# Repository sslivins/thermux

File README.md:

# Thermux

A multi-sensor temperature monitoring system for ESP32-POE boards with Home Assistant integration via MQTT auto-discovery. **Supports 20 DS18B20 sensors on a single 1-Wire bus by default, configurable up to 100** (`CONFIG_MAX_SENSORS`) - perfect for monitoring multiple zones, equipment, or environments from one device.

## Features

- **Up to 100 DS18B20 Sensors** - Monitor multiple temperature points from a single device on one 1-Wire bus (20 by default; raise `CONFIG_MAX_SENSORS` in menuconfig, max 100)
- **Optimized Parallel Reads** - Uses 1-Wire skip ROM command to read all sensors simultaneously (~1050ms for 20 sensors in 12-bit mode, ~450ms in 9-bit)
- **Home Assistant Integration** - MQTT auto-discovery for seamless integration
- **Modbus TCP** - Optional read-only Modbus TCP server so PLCs and heat pump controllers can read temperatures directly (see [Modbus TCP](#modbus-tcp))
- **BACnet/IP** - Optional read-only BACnet/IP server for building-automation systems (see [BACnet/IP](#bacnetip))
- **Web Interface** - Configuration and monitoring via built-in web server
- **Sensor Identification** - Change detection highlighting helps identify which physical sensor is which
- **Custom Sensor Names** - Assign friendly names to sensors via web UI (persisted in NVS)
- **OTA Updates** - Over-the-air firmware updates from GitHub releases or manual upload with progress display, including a native Home Assistant firmware **update entity** with an Install button and progress bar
- **Ethernet & WiFi** - Primary Ethernet with WiFi fallback
- **mDNS** - Access via `thermux.local` (auto-increments on collision: thermux-2.local, etc.)
- **Service Discovery** - Discoverable via `_thermux._tcp` and `_http._tcp` services
- **Web-based Logs** - View system logs without serial connection (16KB circular buffer)
- **Bus Error Tracking** - Monitor 1-Wire CRC error rates per sensor and globally via web UI and Home Assistant
- **Runtime Log Level Control** - Change log verbosity via web UI without reflashing
- **Session-based Authentication** - Optional password protection with login page
- **API Key Authentication** - Stateless API access for scripts and automation

## Hardware Requirements

- **Board**: [Olimex ESP32-POE-ISO](https://www.olimex.com/Products/IoT/ESP32/ESP32-POE-ISO/) (or compatible ESP32-POE board)
- **Sensors**: DS18B20 1-Wire temperature sensors
- **Connection**: Sensors connected to GPIO4 (configurable in menuconfig)
- **PCB** (optional): Custom breakout board - see [hardware/](hardware/) for KiCad files and BOM
- **Enclosure** (optional): 3D printable case - see [enclosure/](enclosure/) for print files

### Wiring

| DS18B20 Pin | ESP32-POE |
|-------------|-----------|
| VCC (Red)   | 3.3V      |
| GND (Black) | GND       |
| DATA (Yellow) | GPIO4   |

> **Note**: A 4.7kΩ pull-up resistor is required between DATA and VCC. For 10+ sensors, use 2.2kΩ or 1.5kΩ to ensure reliable bus communication (the ESP32's internal pull-up is too weak for 1-Wire).

## Installation

### Pre-built Firmware (Recommended)

Download the latest firmware from [GitHub Releases](https://github.com/sslivins/thermux/releases/latest) and follow the [FLASHING.md](FLASHING.md) guide.

**For brand new ESP32-POE devices**, you'll need all three files:
- `bootloader.bin`
- `partition-table.bin`
- `thermux.bin`

**For OTA updates** on devices already running Thermux, use the web interface at `http://thermux.local/ota` - it downloads and installs updates automatically (no manual file download needed). You can also manually upload a specific `thermux.bin` version if desired.

See [FLASHING.md](FLASHING.md) for detailed instructions.

### Building from Source

#### Prerequisites

- [ESP-IDF v5.5.x](https://docs.espressif.com/projects/esp-idf/en/latest/esp32/get-started/)
- VS Code with ESP-IDF extension (recommended)

#### Build & Flash

```bash
# Set target
idf.py set-target esp32

# Build
idf.py build

# Flash
idf.py -p COMx flash monitor
```

Or use the ESP-IDF VS Code extension build/flash commands.

## Configuration

After flashing, access the web interface at `http://thermux.local` or the device IP.

> **Note**: If multiple devices are on the network, subsequent devices will be `thermux-2.local`, `thermux-3.local`, etc.

### Web Interface Pages

- **/** - Dashboard with live temperature readings
- **/config** - Configuration settings (MQTT, WiFi, sensor intervals, OTA)
- **/ota** - Manual firmware upload

### Configuration Options

| Setting | Description |
|---------|-------------|
| **MQTT Broker** | Home Assistant MQTT broker address |
| **MQTT Port** | Broker port (default: 1883) |
| **MQTT Username/Password** | Authentication credentials |
| **WiFi SSID/Password** | Fallback WiFi credentials |
| **Read Interval** | Sensor polling interval (seconds) |
| **Publish Interval** | MQTT publish interval (seconds) |
| **OTA URL** | GitHub releases URL for automatic updates |
| **Security** | Enable/disable password protection |

## REST API

Full API documentation is available as an OpenAPI 3.1 spec: [`docs/openapi.yaml`](docs/openapi.yaml)

View it interactively: [Swagger Editor](https://editor.swagger.io/?url=https://raw.githubusercontent.com/sslivins/thermux/main/docs/openapi.yaml)

## Home Assistant Integration

The device automatically registers sensors with Home Assistant via MQTT discovery. Each sensor appears as a temperature entity. Diagnostics include network status, uptime, seconds since the last successful bus read, consecutive failed bus cycles, and a rolling error rate across the most recent 1,000 reads. Lifetime read counters remain available as disabled-by-default engineering diagnostics.

### Firmware Update Entity

Thermux publishes a native Home Assistant **`update` entity** (device class `firmware`) via MQTT discovery. It shows the installed version, the latest available GitHub release, a link to the release notes, and an **Install** button that triggers the OTA download **with a live progress bar** — the same experience as updating any other HA device, no automation or REST command needed.

The entity is backed by these MQTT topics (base topic configurable, default `thermux`):

| Topic | Direction | Purpose |
|-------|-----------|---------|
| `homeassistant/update/thermux_firmware/config` | retained | Discovery config |
| `thermux/update/state` | device → HA (retained) | JSON: `installed_version`, `latest_version`, `release_url`, `update_percentage`, `in_progress` |
| `thermux/update/install` | HA → device | Payload `install` starts the OTA |

The device checks GitHub for new releases periodically (see `OTA_CHECK_INTERVAL_HOURS`) and updates the entity whenever availability or download progress changes.

### Manual REST Integration (Optional)

You can also poll sensors directly:

```yaml
# configuration.yaml
rest:
  - resource: http://thermux.local/api/sensors
    scan_interval: 60
    sensor:
      - name: "Temperature Sensor 1"
        value_template: "{{ value_json[0].temperature }}"
        unit_of_measurement: "°C"
        device_class: temperature
```

## Modbus TCP

Thermux can run a small, **read-only** Modbus TCP server so a PLC or heat pump controller can read temperatures without HTTP or JSON. It's off by default: turn it on under **Settings → Modbus TCP**, where you can also set the port (default 502) and unit ID (default 1).

Modbus has no password. Anyone on the network can read the registers, but nothing can be changed over Modbus, so only enable it on a network you trust.

### Sensor channels

Each sensor gets a **channel** (0–99) the first time it's seen, keyed by its ROM ID. A sensor keeps its channel when other sensors are added or removed, so a register address (and BACnet object) always refers to the same physical sensor. New sensors fill the lowest free channels, in ROM ID order. Modbus TCP and BACnet/IP share the same channels: channel N is input register 100+N and BACnet Analog Input N.

The **Settings → Sensor Channels** section shows each channel's Modbus register, BACnet object, sensor, and the status and temperature clients are currently reading. From there you can:

- **Move** a sensor to another channel. If that channel is in use, the two sensors swap.
- **Release** the channel of a sensor that has been disconnected, so the channel can be reused. Channels of connected sensors can't be released; they would just be reassigned on the next read.

Channels and Modbus settings are included in backups (**Settings → Backup**), so a replacement Thermux can serve the same register map.

### Register map

All registers are **input registers**, read with function code 04. Addresses are zero-based. All 100 channels are always mapped, whatever `CONFIG_MAX_SENSORS` is set to, so the map never changes between builds.

| Address | Contents |
|---------|----------|
| 0 | Map version (currently 1) |
| 1–3 | Firmware version: major, minor, patch |
| 4 | Channel capacity (always 100) |
| 5 | Read-cycle counter. Goes up by one after every scheduled read attempt, including failed ones; wraps at 65535 |
| 6–7 | Uptime in seconds (32-bit, register 6 is the high word) |
| 8–10 | Ethernet MAC address, two bytes per register (register 8 = byte 0 << 8 \| byte 1) |
| 11 | Firmware sensor limit (`CONFIG_MAX_SENSORS`) |
| 12 | Number of channels in use |
| 13 | Number of sensors found on the bus |
| 14 | Result of the last read cycle: 0 OK, 1 some sensors failed, 2 bus failure, 3 no sensors |
| 15 | Read interval in seconds |
| 100 + channel | Temperature in hundredths of a °C, signed 16-bit (2150 = 21.50 °C, 0xFF38 = −2.00 °C). **0x8000 whenever the status isn't OK** |
| 200 + channel | Status (see below) |
| 300 + channel | Seconds since the last successful read (capped at 65534). 65535 if the sensor has never been read or isn't connected |
| 1000 + 4 × channel | ROM ID, 4 registers per channel, two bytes per register in the same order as the address shown in the UI and API |

Channel status, checked in this order:

| Value | Meaning |
|-------|---------|
| 1 | Unassigned: no sensor in this channel |
| 2 | Missing: the sensor wasn't found in the latest bus scan |
| 3 | Read error: the sensor's latest read failed, or the whole read cycle failed |
| 4 | Stale: never read successfully, or the last good reading is older than 3 × the read interval (at least 30 s) |
| 0 | OK |

Use the age registers if you need a stricter freshness limit than the stale rule.

Each block (0–15, 100–199, 200–299, 300–399, 1000–1399) is separate. A read that covers an address outside those blocks, or runs from one block into the next, returns exception 0x02 (illegal data address). A single read can cover at most 125 registers, so the ROM block takes four reads.

### Reading a consistent set

A reading cycle can finish between two of your requests. To be sure the values you read all come from the same cycle, read register 5, read the blocks you need, then read register 5 again. If it changed, read again.

### Unit ID and errors

- Address requests to the configured unit ID (default 1). Unit ID 0 is also answered.
- Requests for any other unit ID get exception 0x0B (gateway target device failed to respond).
- Unit ID 255 isn't answered: the Modbus library Thermux uses (esp-modbus 2.1.3) drops it before it reaches the server. A fix has been submitted upstream ([espressif/esp-modbus#190](https://github.com/espressif/esp-modbus/pull/190)).
- Every function code other than 04, including all writes, gets exception 0x01 (illegal function).
- Up to 3 clients can be connected at once.

### Discovery

While the server is running, Thermux advertises it over mDNS as `_mbap._tcp`, with TXT records `unit` (unit ID), `id` (MAC address) and `map` (map version). Most PLCs don't use mDNS, so you'll usually enter the IP address and port by hand; give Thermux a DHCP reservation so the address doesn't change.

### Examples

The repo includes a small reader, `scripts/thermux_modbus.py` (needs `pip install pymodbus`). With just an address it decodes the whole map; `channel` reads specific channels; `raw` reads any range from any Modbus TCP device:

```bash
python scripts/thermux_modbus.py thermux.local               # device info + every channel
python scripts/thermux_modbus.py thermux.local --watch 5     # repeat every 5 s
python scripts/thermux_modbus.py thermux.local channel 3     # one channel: temperature, status, age, ROM ID
python scripts/thermux_modbus.py thermux.local channel 3 7   # several channels
python scripts/thermux_modbus.py thermux.local channel 3 --value   # just the °C value, for scripts
python scripts/thermux_modbus.py 192.168.1.50 --port 502 --unit 1 raw 100 6          # input registers
python scripts/thermux_modbus.py 192.168.1.50 raw 0 10 --fc 3                        # holding registers
```

[mbpoll](https://github.com/epsilonrt/mbpoll), temperatures of channels 0–5 (`-0` makes addresses zero-based):

```bash
mbpoll -m tcp -a 1 -0 -t 3 -r 100 -c 6 -1 thermux.local
```

Python with [pymodbus](https://github.com/pymodbus-dev/pymodbus) 3.9 or later (older versions use `slave=` instead of `device_id=`):

```python
from pymodbus.client import ModbusTcpClient

client = ModbusTcpClient("thermux.local", port=502)
client.connect()

def read(address, count):
    result = client.read_input_registers(address, count=count, device_id=1)
    if result.isError():
        raise RuntimeError(result)
    return result.registers

while True:
    cycle = read(5, 1)[0]
    temps = read(100, 10)
    status = read(200, 10)
    if read(5, 1)[0] == cycle:
        break

for channel, (raw, st) in enumerate(zip(temps, status)):
    if st == 0:
        celsius = (raw - 65536 if raw >= 32768 else raw) / 100
        print(f"channel {channel}: {celsius:.2f} °C")
```

## BACnet/IP

Thermux can also run a **read-only** BACnet/IP server, for building-automation systems that speak BACnet rather than Modbus. It's off by default: turn it on under **Settings → BACnet/IP**. Modbus and BACnet can run at the same time and serve the same sensor channels.

| Setting | Default | Notes |
|---------|---------|-------|
| UDP port | 47808 (0xBAC0) | The standard BACnet/IP port. Can't be the web server's port |
| Device instance | Derived from the Ethernet MAC | 0–4194302. Must be unique on the BACnet network, so set it by hand if your site has a numbering plan |
| Device name | The hostname | Up to 63 characters |

Like Modbus, BACnet has no password. Anyone on the network can read the objects, but nothing can be changed, so only enable it on a building-controls network you trust.

### Objects

The **Device** object reports vendor and model `Thermux`, the firmware version, and an object list.

Each assigned [sensor channel](#sensor-channels) is an **Analog Input**, and the instance number is the channel number. AI 3 is always channel 3, which is Modbus register 103. Unassigned channels have no object, so the object list only shows channels with a sensor.

| Property | Value |
|----------|-------|
| Object name | The sensor's friendly name, or `Channel N` if it has none. If two sensors have the same name, the second gets ` (N)` added, because BACnet object names must be unique |
| Description | The sensor's ROM ID, for example `281491BA00000069` |
| Present value | Temperature in °C. If a reading fails, the last good value stays and Reliability shows the fault |
| Units | degrees-Celsius |
| Reliability | `no-fault-detected` when OK; `no-sensor` when the sensor is missing; `communication-failure` on a read error; `unreliable-other` when the reading is stale |
| Status flags | `fault` is set whenever Reliability isn't `no-fault-detected` |
| COV increment | 0.1 °C |

When sensors are added, removed or renamed, the object list changes and the device's Database Revision goes up, so clients that cache the object list know to read it again.

### Services

- Who-Is / I-Am and Who-Has / I-Have
- ReadProperty and ReadPropertyMultiple
- SubscribeCOV (confirmed and unconfirmed), up to 16 subscriptions at once. Thermux sends a notification whenever a temperature changes by 0.1 °C or more, or its status flags change.

All write and management services (WriteProperty, CreateObject, ReinitializeDevice, DeviceCommunicationControl and so on) are rejected with `unrecognized-service`.

If the device's IP address changes (a new DHCP lease, for example), Thermux notices within a few seconds and sends a new I-Am. You don't need to restart anything.

### Example

The repo includes `scripts/thermux_bacnet.py`, which needs [BAC0](https://github.com/ChristianTremblay/BAC0) 2025 or later (`pip install BAC0`):

```bash
python scripts/thermux_bacnet.py --discover                       # Who-Is on the local network
python scripts/thermux_bacnet.py 192.168.1.50                     # device info and every Analog Input
python scripts/thermux_bacnet.py 192.168.1.50 --cov 60            # watch COV notifications for a minute
python scripts/thermux_bacnet.py 192.168.1.50 --try-write         # check that writes are rejected
python scripts/thermux_bacnet.py 192.168.1.50 --port 47809        # non-standard port
```

Add `--local 192.168.1.32/24` (your PC's address) if the script picks the wrong network interface. Who-Is discovery only finds devices on port 47808. On another port, I-Am replies are broadcast to that port, so give the address and `--port` instead.

## OTA Updates

Thermux can update three ways: the native Home Assistant **update entity** (above), the built-in **web interface**, or a **manual `.bin` upload**.

### Automatic Updates (Recommended)

The web interface can automatically download and install updates from GitHub releases:

1. Configure the OTA URL in web settings: `https://api.github.com/repos/sslivins/thermux/releases/latest`
2. Go to the OTA page and click "Check for Updates"
3. If a newer version is available, click "Update Now"
4. The device downloads, flashes, and reboots automatically - **no manual file download needed**

### Manual Upload

To install a **specific version** or **older version**, use the manual upload feature:

1. Download the desired `thermux.bin` from any [release](https://github.com/sslivins/thermux/releases)
2. Navigate to `/ota` page
3. Select the `.bin` firmware file
4. Click "Upload & Flash"

## Security

By default, the web interface is open (no authentication required). To enable password protection:

1. Go to `/config` → Security section
2. Check "Enable password protection"
3. Set username and password
4. Click "Save Security Settings"

When enabled, unauthorized access redirects to a login page. Sessions are stored in a cookie and expire after 7 days.

### API Key Authentication

For scripts and automation, use the API key instead of session cookies:

```bash
# Get sensor readings
curl -H "X-API-Key: YOUR_API_KEY" http://thermux.local/api/sensors

# Get device status
curl -H "X-API-Key: YOUR_API_KEY" http://thermux.local/api/status
```

The API key is:
- **Auto-generated** when authentication is first enabled
- **Visible** in Settings → Security section (click 📋 to copy)
- **Regeneratable** if compromised (click 🔄 to generate new key)
- **Persisted** across reboots in NVS flash

### Session Authentication

For browser-based access, the web UI uses session cookies. Protected API endpoints return `401 Unauthorized` with JSON body containing `{"login_required": true}` when not authenticated.

#### Auth Endpoints

| Endpoint | Method | Description |
|----------|--------|-------------|
| `/login` | GET | Login page (no auth required) |
| `/api/auth/login` | POST | Authenticate with `{"username":"...", "password":"..."}` |
| `/api/auth/logout` | POST | Destroy session |
| `/api/auth/status` | GET | Check if logged in |
| `/api/config/auth` | GET | Get auth config (includes API key) |
| `/api/config/auth/regenerate-key` | POST | Generate new API key |

### Home Assistant Integration

With API key authentication, REST integrations are straightforward:

```yaml
# configuration.yaml
rest:
  - resource: http://thermux.local/api/sensors
    headers:
      X-API-Key: "your-api-key-here"
    sensor:
      - name: "Pool Temperature"
        value_template: "{{ value_json.sensors[0].temperature }}"
        unit_of_measurement: "°C"
```

Alternatively, use the built-in MQTT integration with Home Assistant auto-discovery (no API key needed for MQTT).

## Technical Notes

### Optimized Temperature Reading

The firmware uses the 1-Wire **skip ROM** command (`0xCC`) to trigger temperature conversion on all DS18B20 sensors simultaneously, then reads each sensor individually. This reduces read time from O(n × delay) to O(delay + n × read):

| Sensors | Sequential (12-bit) | Parallel (12-bit) | Parallel (9-bit) |
|---------|---------------------|-------------------|-------------------|
| 1       | ~800ms              | ~800ms            | ~100ms            |
| 5       | ~4000ms             | ~850ms            | ~150ms            |
| 10      | ~8000ms             | ~900ms            | ~250ms            |
| 20      | ~16000ms            | ~1050ms           | ~450ms            |

The conversion delay depends on resolution: 12-bit = 750ms, 11-bit = 375ms, 10-bit = 188ms, 9-bit = 94ms. The parallel read overhead per sensor is minimal (~25ms for bus communication).

### Log Buffer

A 16KB circular buffer captures ESP-IDF logs for web display. Noisy system components (HTTP server internals, Ethernet MAC, etc.) are filtered to keep logs useful. The buffer can be viewed, cleared, and downloaded from the config page.

## Hardware Design

This repository includes open-source hardware designs:

### PCB ([hardware/](hardware/))

Two open-source KiCad boards:

- **Sensor Bus Hat** - plugs onto the ESP32-POE-ISO and breaks the 1-Wire bus out to RJ45 (carries the bus pull-up resistor)
- **Temperature Node** - DS18B20 breakout with RJ45 connectors for daisy-chaining sensors

- **KiCad project files** - Full schematic and PCB layout
- **Gerber files** - Ready for fabrication (JLCPCB, PCBWay, etc.)
- **Bill of Materials** - DigiKey part links

### Enclosure ([enclosure/](enclosure/))

3D printable cases, in two parts:

- **ESP32-POE-ISO Case** - the main enclosure; houses the ESP32-POE-ISO with the Sensor Bus Hat plugged on
- **Temperature Node** - two-part case (PCB + enclosure) for a distributed DS18B20 sensor node on the 1-Wire bus

Each is provided as:

- **Fusion 360** (.f3d / .f3z) - Parametric source files
- **STEP** (.step) - Universal CAD interchange format
- **Print files** (.3mf, .stl) - Ready for slicing

## Version History

See [GitHub Releases](https://github.com/sslivins/thermux/releases) for changelog.

## License

MIT License - See [LICENSE](LICENSE) for details.

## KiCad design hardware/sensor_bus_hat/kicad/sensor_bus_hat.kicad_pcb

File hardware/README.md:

# Hardware

Open-source PCB design files for Thermux. There are **two** boards:

- **Sensor Bus Hat** ([`sensor_bus_hat/`](sensor_bus_hat/)) — plugs onto the
  Olimex ESP32-POE-ISO and breaks the 1-Wire bus out to an RJ45 jack, carrying
  the bus pull-up resistor.
- **Temperature Node** ([`temp_node/`](temp_node/)) — the distributed DS18B20
  sensor breakout with RJ45 connectors for daisy-chaining sensors along the bus.

## Directory Structure

```
hardware/
├── sensor_bus_hat/     # ESP32-POE-ISO bus-adapter hat
│   ├── kicad/          # KiCad project (.kicad_pro, .kicad_sch, .kicad_pcb)
│   └── gerbers/        # Manufacturing files (gerbers, drills, BOM, CPL)
├── temp_node/          # DS18B20 sensor breakout node
│   ├── kicad/
│   └── gerbers/
└── README.md
```

Each board's `gerbers/` folder is self-contained — zip its contents (or upload
the folder) to JLCPCB / PCBWay to fabricate that board.

## Sensor Bus Hat

Adapter board that sits on the Olimex ESP32-POE-ISO and exposes the 1-Wire bus
on an RJ45 jack. It carries the bus **pull-up resistor** (see the pull-up note
below).

### Bill of Materials

| Qty | Designator | Description | Part Number |
|-----|-----------|-------------|-------------|
| 1 | R1 | Pull-up resistor, 4.7 kΩ (0805) — see pull-up note | (generic) |
| 1 | J1 | RJ45 Connector | GCT MJ3225-88-0 |
| 1 | J2 | 10-pin 2.54 mm pin socket (to ESP32-POE-ISO) | (generic) |

> **Pull-up note:** R1 is populated as **4.7 kΩ**, which is correct for a small
> bus. For **10+ sensors** on a long bus, drop to **2.2 kΩ or 1.5 kΩ** (a
> *lower* resistance = stronger pull-up) for reliable 1-Wire communication — the
> ESP32's internal pull-up alone is too weak.

## Temperature Node

Custom breakout board with RJ45 connectors for daisy-chaining DS18B20 sensors.

### PCB Features

- DS18B20 sensor breakout
- Screw terminal connections
- Compatible with Olimex ESP32-POE-ISO

### Bill of Materials

| Qty | Description | Part Number | DigiKey Link |
|-----|-------------|-------------|--------------|
| 2 | RJ45 Connector | GCT MJ3225-88-0 | [MJ3225-88-0](https://www.digikey.com/en/products/detail/gct/MJ3225-88-0/16893750) |
| 1 | JST XH Header (3-pin) | JST S3B-XH-A | [S3B-XH-A](https://www.digikey.com/en/products/detail/jst-sales-america-inc/S3B-XH-A/1651048) |
| 1 | PTC Resettable Fuse | Murata PRG21AR420MS1RA | [PRG21AR420MS1RA](https://www.digikey.com/en/products/detail/murata-electronics/PRG21AR420MS1RA/2595394) |
| 1 | 10µF Capacitor (0805) | Samsung CL21B106KOQNNNE | [CL21B106KOQNNNE](https://www.digikey.com/en/products/detail/samsung-electro-mechanics/CL21B106KOQNNNE/3888530) |
| 1 | 0.1µF Capacitor (0805) | Samsung CL21B104KBCNNNC | [CL21B104KBCNNNC](https://www.digikey.com/en/products/detail/samsung-electro-mechanics/CL21B104KBCNNNC/3886661) |

## Manufacturing

Gerber files are ready for fabrication at JLCPCB, PCBWay, or similar services.

## License

Hardware designs are released under [CERN-OHL-P v2](https://ohwr.org/cern_ohl_p_v2.txt) (Permissive).

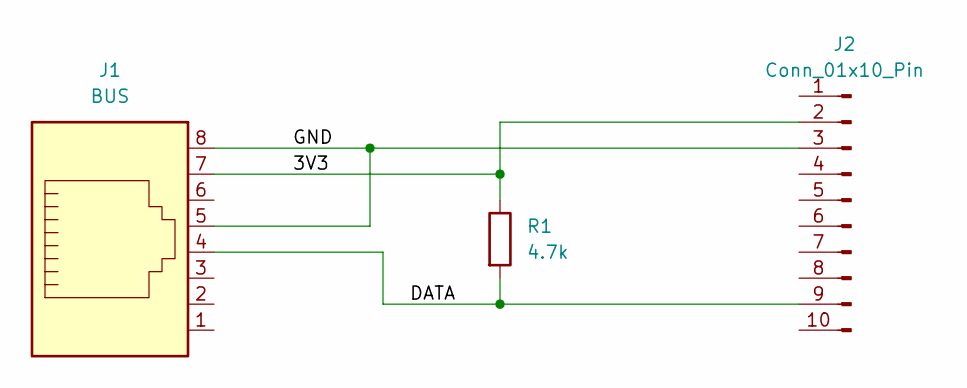
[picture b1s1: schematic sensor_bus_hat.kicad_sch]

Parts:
J1: BUS; GCT_MJ3225-88-0_REVA
J2: Conn_01x10_Pin; PinSocket_1x10_P2.54mm_Vertical
R1: 4.7k; R_0805_2012Metric

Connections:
/3V3: J1.7, J2.2, R1.1
/DATA: J1.4, J2.9, R1.2
/GND: J1.5, J1.8, J2.3

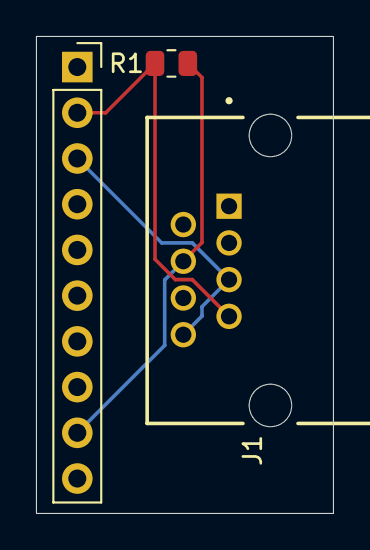
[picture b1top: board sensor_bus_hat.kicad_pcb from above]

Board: 2 copper layers, 16.5 x 26.5 mm, 3 parts (0 on the bottom side), 3 nets.

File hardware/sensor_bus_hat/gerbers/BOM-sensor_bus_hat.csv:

Comment,Designator,Footprint,LCSC,Quantity
4.7k,R1,R_0805_2012Metric,,1
Conn_01x10_Pin,J2,PinSocket_1x10_P2.54mm_Vertical,,1
BUS,J1,GCT_MJ3225-88-0_REVA,,1

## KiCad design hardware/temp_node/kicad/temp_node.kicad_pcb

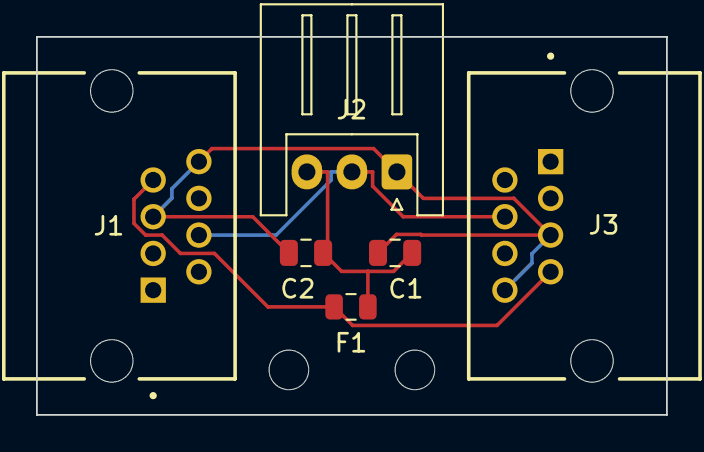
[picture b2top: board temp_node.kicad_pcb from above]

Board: 2 copper layers, 35.0 x 21.0 mm, 8 parts (0 on the bottom side), 4 nets.

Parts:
C1: 10uF; C_0805_2012Metric
C2: 0.1uF; C_0805_2012Metric
F1: PTC 54mA/100mA (resettable); Fuse_0805_2012Metric
H0, H1: MountingHole_2.2mm_M2
J1: TEMP_BUS_A; GCT_MJ3225-88-0_REVA
J2: TEMP_SENSOR; JST_XH_S3B-XH-A_1x03_P2.50mm_Horizontal
J3: TEMP_BUS_B; GCT_MJ3225-88-0_REVA

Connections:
/1WIRE_DATA: J1.4, J2.2, J3.4
/3V3_BUS: F1.1, J1.7, J3.7
/3V3_NODE: C1.2, C2.2, F1.2, J2.3
GND: C1.1, C2.1, J1.5, J1.8, J2.1, J3.5, J3.8

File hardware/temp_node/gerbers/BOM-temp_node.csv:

Comment,Designator,Footprint,LCSC,Quantity
TEMP_BUS_A,J1,GCT_MJ3225-88-0_REVA,,1
TEMP_SENSOR,J2,JST_XH_S3B-XH-A_1x03_P2.50mm_Horizontal,,1
PTC 54mA/100mA (resettable),F1,Fuse_0805_2012Metric,,1
TEMP_BUS_B,J3,GCT_MJ3225-88-0_REVA,,1
0.1uF,C2,C_0805_2012Metric,,1
10uF,C1,C_0805_2012Metric,,1

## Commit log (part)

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2026-01-28 added gitignore
2026-01-29 improved settings page, fixed some issues with friendly names
2026-01-29 bumped version
2026-01-30 fixed manual update
2026-01-30 added wifi ssid scanning
2026-01-30 added a log viewer to the config page
2026-01-30 friendly name buffer was being used after freed causing corruption to the friendly name
2026-01-30 added the option to sort sensors by temperature change to make it easier to find a sensor
2026-01-30 Fix disabled button hover effects
    - Add pointer-events: none to .btn:disabled to prevent mouse interactions
    - Simplify hover selectors (remove :not(:disabled) since pointer-events handles it)
    - Affects Install Update and Upload Firmware buttons when disabled
2026-01-30 increased uri handlers
2026-01-30 added test infrastructure
2026-01-30 change logic of when to build images
2026-01-31 finally fixed firmware update check, removed custom minify and use one from python instead
2026-01-31 finally fixed firmware update check, removed custom minify and use one from python instead (#13)
2026-01-31 bump version
2026-01-31 improving upgrade status
2026-01-31 improving upgrade status (#14)
2026-01-31 fixed mqtt connected status color
2026-01-31 Fix firmware progress (#16)
    * firmware progress is much better now for both manual and github updates
    * fixed mqtt connected status color
2026-01-31 improved network status and send this info to home assistant as well (#17)
2026-02-01 clean up logs and log levels. add log level control from web ui
2026-02-01 reduced info level logging a little
2026-02-01 added basic auth, bumped version to 1.1 (#19)
2026-02-01 remaned to thermux (#20)
2026-02-01 fixed firmware update which couldnt check when the device was rebooting because of auth
2026-02-01 added api key rather than using user/password and sessions cookie to acess the api
2026-02-01 added api key rather than using user/password and sessions cookie to … (#22)
    * added api key rather than using user/password and sessions cookie to acess the api
    * updated readme
2026-02-01 Added pcb and models (#23)
    * added pcb files for temperature nodes as well as model files for the tempereature node case
    * updated main readme
2026-02-02 support up to 4 concurrent sessions instead of 1
2026-02-02 increased session length to 7 days, up from 24h
2026-02-03 added new workflow to create tag based on app_version
2026-02-03 give write permissions
2026-02-11 Switch from HTML minification to gzip compression
    - Replace html_minifier.py with gzip_html.py (based on arctic-controller)
    - Change EMBED_TXTFILES to EMBED_FILES for binary gzipped data
    - Add Content-Encoding: gzip header when serving HTML pages
    - Gzip gives ~75% reduction vs ~20% from minification
    - No runtime CPU cost on ESP32 (browser decompresses)
    - Removes minify-html Python dependency
2026-02-11 Fix password reveal icon visibility on dark backgrounds
    - Add filter:invert(1) for ::-ms-reveal (Edge) and ::-webkit-credentials-auto-fill-button (Chrome)
    - Applied to both config page and login page
2026-02-11 Add 1-Wire bus error rate tracking, bump to 2.1.0
    - Track total reads and failed reads (CRC errors) in onewire_temp
    - Expose bus_stats (total_reads, failed_reads, error_rate%) in /api/status
    - Add POST /api/sensors/error-stats/reset endpoint to clear counters
    - Display error rate in dashboard status bar with color coding
    - Click error stats to reset counters
    - Auto-refresh stats with sensor readings every 5s
2026-02-11 Add per-sensor error tracking and publish bus stats to Home Assistant
    - Track total_reads and failed_reads per sensor in onewire_sensor_t
    - Expose per-sensor error stats in /api/sensors response
    - Display per-sensor error rate on dashboard sensor cards
    - Register 3 HA diagnostic entities: Bus Error Rate (%), Total Reads, Failed Reads
    - Publish bus error stats via MQTT alongside network diagnostics
2026-02-12 Add per-sensor error stats to OpenAPI Sensor schema
2026-02-12 Replace inline API docs with OpenAPI spec link and Swagger viewer
2026-02-12 Add max sensor limit warning, bump to 2.2.0
    - Log warning when scan reaches CONFIG_MAX_SENSORS limit
    - Add max_sensors field to /api/status response
    - Show amber warning banner on dashboard when at sensor limit
    - Update OpenAPI spec with max_sensors field
2026-02-12 Update README with measured 20-sensor read times (12-bit and 9-bit)
2026-02-13 Add sort by error rate option, bump to 2.4.0 (#29)
    - Add 'Error Rate' option to sensor sort dropdown
    - Sorts sensors by failed_reads/total_reads (highest first)
    - Useful for identifying problematic sensors at a glance
2026-02-14 Add per-sensor error stats reset and bump to v2.5.0
    - Bus error rate click now resets both global and all per-sensor stats
    - Per-sensor error rate on each card is now clickable to reset individually
    - New API endpoint: POST /api/sensors/{address}/error-stats/reset
    - Added sensor_manager_reset_all_error_stats() and sensor_manager_reset_sensor_error_stats()
    - Bump version to 2.5.0
2026-02-14 Add per-sensor error-stats/reset endpoint to OpenAPI spec
2026-02-14 Redesign firmware update UI with Cloud/File tabs
    - Replace disorganized layout with two clear source tabs: Cloud and Local File
    - Single 'Install Update' button that works for whichever source is active
    - Cloud tab: check for updates, shows latest version and availability
    - File tab: file picker for manual .bin uploads (downgrades, custom builds)
    - Shared progress bar and status message at bottom, only visible during install
    - Tabs lock during active update to prevent confusion
